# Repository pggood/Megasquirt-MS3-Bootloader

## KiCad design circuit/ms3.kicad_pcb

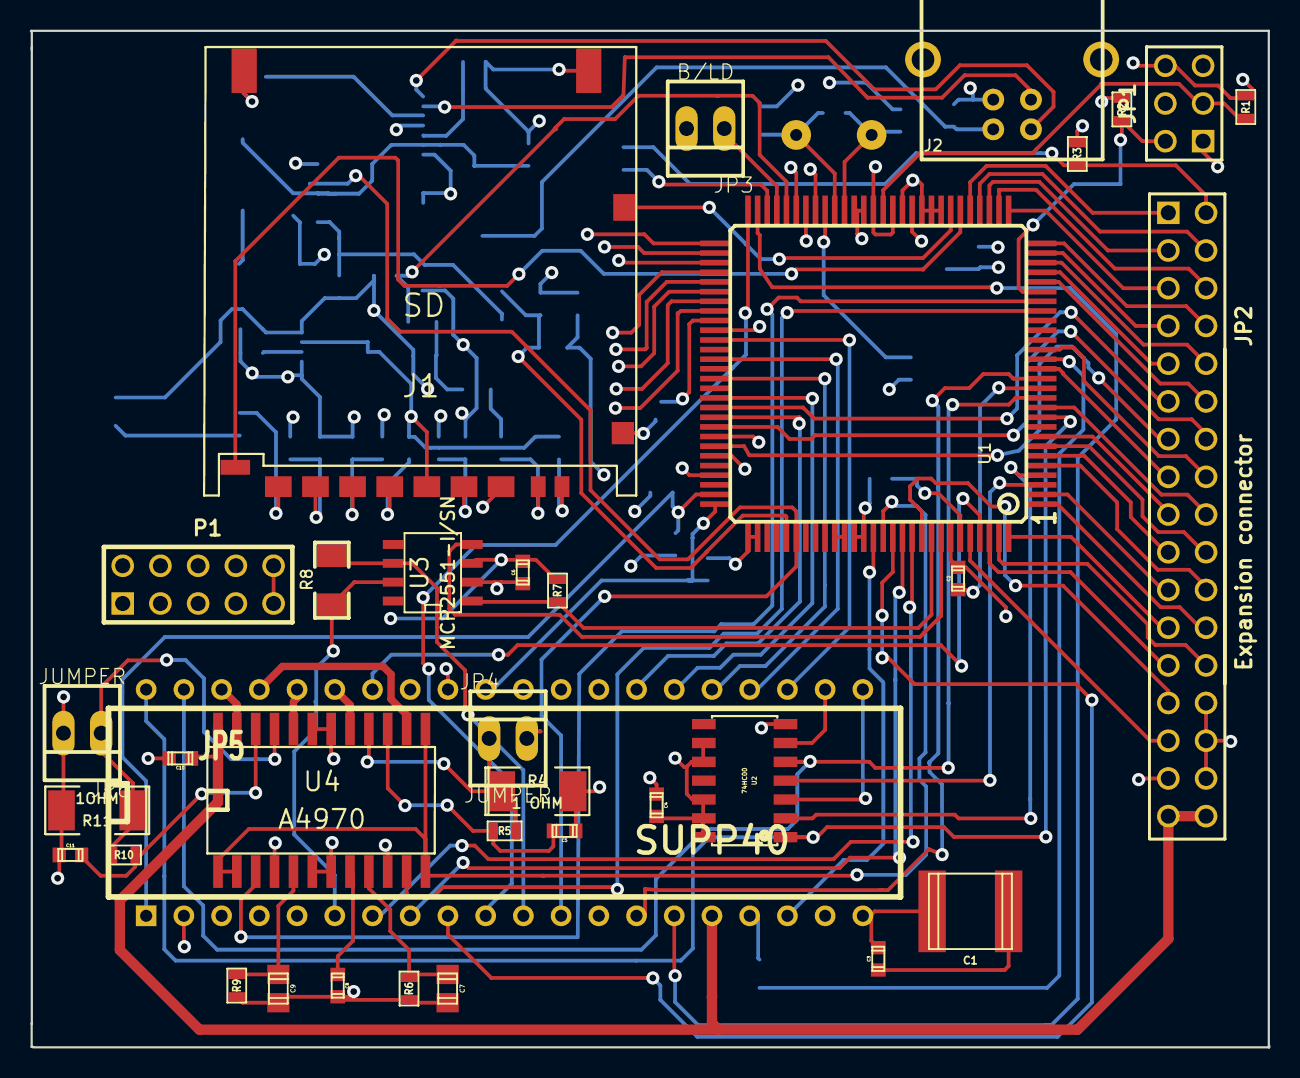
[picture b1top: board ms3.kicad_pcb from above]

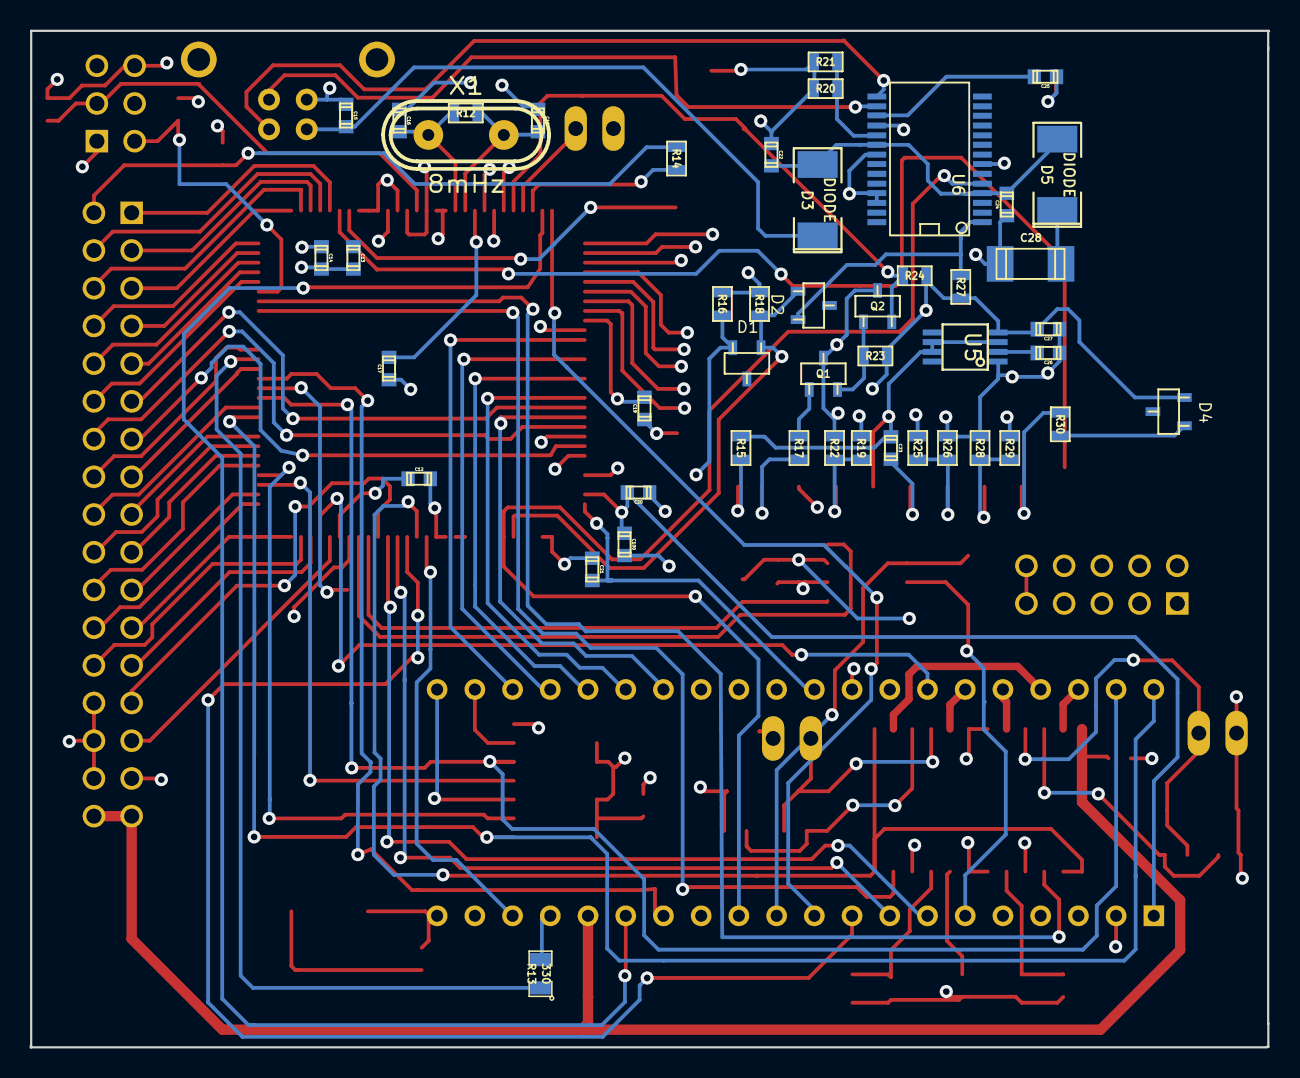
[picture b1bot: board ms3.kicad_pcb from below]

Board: 4 copper layers, 83.4 x 68.5 mm, 82 parts (47 on the bottom side), 123 nets.

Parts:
C1: 4.5uF; c_2220
C2, C21: 90nF; c_0603
C3, C4, C6, C20: .1; c_0603
C5, C11: 1nF; c_0603
C7, C9: 55nF; c_0805
C8, C10: 1.5uF; c_0603
C12, C13, C14, C100: .1uF; c_0603
C15: 10nF; c_0603
C16, C18: 50pF; c_0603
C17, C19: .2uF; c_0603
C22: 185nF; c_0603
C23, C26, C27: 1uF; c_0603
C24: 186nF; c_0603
C25: 100N; c_0603
C28: 4.7uF; c_1808
D1, D2, D4: DIODE; sot23
D3, D5: DIODE; SM2010
J1: SD; SDCARDmolex130203a
J2: USB_B
JP1: CONN_3X2; pin_array_3x2
JP2: Expansion connector; pin_array_17x2
JP3: B/LD; PINHEAD1-2
JP4, JP6: JUMPER; PINHEAD1-2
JP5: SUPP40; DIP-40__600
P1: CONN_5X2; PIN_ARRAY_5x2
Q1, Q2: 2N7002; sot23_v2
R1, R2, R21: 4K7; SM0603
R3, R14, R15, R16, R18, R20, R27: 10K; SM0603
R4: 1 OHM; SM2010
R5, R6, R7, R9, R10, R22, R23, R24, R26, R28: 1K; SM0603
R8: 120; SM1206
R11: 1OHM; SM2010
R12: 10M; SM0603
R13: 330; SM0805
R17, R19, R25, R29: 470; SM0603
R30: 10k; SM0603
U1: MC9S12XDP512; PQFP112
U2: 74HC00; SOP14
U3: MCP2551-I/SN; SO8E
U4: A4970; SOICW24
U5: LD1117LD33C; SSOP8
U6: FT232RL; SSOP28
X1: 8mHz; crystal_hc-49u

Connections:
+12V: C10.2, JP2.33, JP2.34, JP5.16, U4.24
/CPU/AD0-1: JP5.23, U1.67
/CPU/AD1-1: JP5.24, U1.69
/CPU/AD2-1: JP5.25, U1.71
/CPU/AD3-1: JP5.26, U1.73
/CPU/AD4-1: JP5.27, U1.75
/CPU/AD5-1: JP5.28, U1.77
/CPU/AD6-1: JP5.29, U1.79
/CPU/AD7-1: JP5.30, U1.81
/CPU/AN11: JP2.11, U1.74
/CPU/AN12: JP2.14, U1.76
/CPU/AN13: JP2.13, U1.78
/CPU/AccLed: JP5.8, U1.101
/CPU/CAM: JP2.18, U1.11
/CPU/CANrx: U1.105, U3.4
/CPU/CANtx: R7.2, U1.104, U3.1
/CPU/FLEX: R14.1, U1.54
/CPU/FP: JP5.33, U1.39
/CPU/IAC1: U1.21, U4.11
/CPU/IAC2: U1.22, U4.3
/CPU/IACEnble: U1.99, U4.1, U4.2, U4.12, U4.13
/CPU/IDLE: JP5.34, U1.109
/CPU/IGN: R13.1, U1.16
/CPU/IGN2: JP2.15, U1.15
/CPU/INJ1: JP5.40, U1.10, U2.1
/CPU/INJ2: JP5.39, U1.12, U2.5
/CPU/IRQ: JP5.15, U1.55
/CPU/InjLed: JP5.7, U1.102
/CPU/KnkEnbl: JP5.18, U1.98
/CPU/PA0: P1.1, U1.57
/CPU/PA1: P1.2, U1.58
/CPU/PA2: P1.3, U1.59
/CPU/PA3: P1.4, U1.60
/CPU/PA4: P1.5, U1.61
/CPU/PA5: P1.6, U1.62
/CPU/PA6: P1.7, U1.63
/CPU/PA7: P1.8, U1.64
/CPU/PB0: JP2.12, U1.24
/CPU/PB1: JP2.9, U1.25
/CPU/PB2: JP2.10, U1.26
/CPU/PB3: JP2.7, U1.27
/CPU/PB4: JP2.8, U1.28
/CPU/PB5: JP2.5, U1.29
/CPU/PB6: JP2.6, U1.30
/CPU/PB7: JP2.3, U1.31
/CPU/PH6: JP2.1, U1.33
/CPU/PH7: JP2.4, U1.32
/CPU/PK0: JP2.17, U1.8
/CPU/PK1: JP2.20, U1.7
/CPU/PK2: JP2.19, U1.6
/CPU/PK3: JP2.22, U1.5
/CPU/PK7: JP2.29, U1.108
/CPU/PM2: JP2.27, U1.103
/CPU/PP2: JP2.21, U1.2
/CPU/PP3: JP2.24, U1.1
/CPU/PP4: JP2.23, U1.112
/CPU/PP5: JP2.26, U1.111
/CPU/PP6: JP2.25, U1.110
/CPU/PT6: JP2.16, U1.17
/CPU/PWM1: U1.4, U2.2
/CPU/PWM2: U1.3, U2.4
/CPU/RESET: JP1.3, R1.1, U1.42
/CPU/RX: D1.1, D2.1, R18.1, U1.89
/CPU/SDCardCS: R29.2, U1.49
/CPU/SDCardInsert: J1.10, U1.34
/CPU/SDCardMISO: Q2.D, R24.2, U1.52
/CPU/SDCardMOSI: R25.2, U1.51
/CPU/SDCardSCLK: R19.2, U1.50
/CPU/TX: JP5.12, U1.90, U6.5
/CPU/VDDA: C20.1, C100.2, JP5.1, U1.83
/CPU/VREF: C21.1, JP5.31, U1.84
/CPU/VSS1: JP5.14, U1.14
/CPU/WarmLed: JP5.9, U1.100
/CPU/XIRQ: JP5.10, U1.56
/SDCARD/3.3V: C23.2, C26.1, J1.4, R15.2, U5.2, U5.3, U5.6, U5.7
/SDCARD/RXMS1: D1.2, JP5.13, R16.2
/SDCARD/SDCardLock: J1.12, U1.35
/ms1Interface/X2: JP5.38, U4.23
/ms1Interface/X3: JP5.37, U4.14
/ms1Interface/X4: JP5.36, U4.20
/ms1Interface/X5: JP5.35, U4.17
GND: C2.1, C4.2, C5.2, C6.2, C7.1, C8.1, C9.1, C10.1, C11.2, C12.1, C14.2, C15.2, C16.2, C17.2, C18.2, C19.2, C20.2, C21.2, C22.2, C23.1, C24.2, C25.2, C26.2, C27.2, C28.2, C100.1, J1.3, J1.6, J1.11, J1.13, J1.14, J2.4, J2.5, JP1.1, JP2.28, JP2.30, JP2.32, JP3.2, JP4.2, JP5.2, JP5.19, JP5.32, JP6.2, Q1.S, Q2.S, R4.2, R6.1, R9.1, R11.2, R20.1, R21.1, R22.2, R26.2, R28.2, U1.36, U1.37, U1.38, U1.40, U1.44, U1.45, U1.66, U1.85, U1.86, U1.94, U1.95, U1.96, U1.97, U1.106, U2.7, U3.2, U4.6, U4.7, U4.18, U4.19, U5.1, U6.7, U6.18, U6.21, U6.25, U6.26
unnamed: JP2.2, R3.1, R14.2
unnamed: P1.9, P1.10
unnamed: C11.1, R10.2, U4.22
unnamed: C5.1, R5.2, U4.15
unnamed: JP6.1, R10.1, R11.1, U4.21
unnamed: JP4.1, R4.1, R5.1, U4.16
unnamed: C1.1, C3.1, JP5.20
unnamed: C1.2, C3.2
unnamed: C7.2, R6.2, U4.9
unnamed: C9.2, R9.2, U4.5
unnamed: JP5.21, U2.3
unnamed: C8.2, U4.8
unnamed: JP5.17, R13.2
unnamed: JP5.6, R8.1, U3.7
unnamed: JP5.11, R8.2, U3.6
unnamed: JP5.22, U2.6
unnamed: C25.1, U6.17
unnamed: D2.2, R27.1, U6.1
unnamed: R20.2, R21.2, U6.19
unnamed: C28.1, D5.1
unnamed: D4.1, R30.1
unnamed: C15.1, D3.1, J2.1
unnamed: J1.2, R25.1, R26.1
unnamed: J1.1, R28.1, R29.1
unnamed: Q1.D, Q2.G, R23.2
unnamed: Q1.G, R17.2
unnamed: J1.5, R19.1, R22.1
unnamed: J1.9, R30.2
unnamed: J1.8, R15.1
unnamed: J1.7, R17.1
unnamed: J2.3, U6.16
unnamed: J2.2, U6.15
unnamed: C22.1, C24.1, D3.2, D5.2, U6.4, U6.20
unnamed: C19.1, U1.65
unnamed: JP3.1, U1.53
unnamed: C17.1, U1.48
unnamed: C16.1, R12.1, U1.46, X1.1
unnamed: C18.1, R12.2, U1.47, X1.2
unnamed: C2.2, U1.13
unnamed: JP1.2, R2.2, U1.23
VCC: C4.1, C6.1, C12.2, C13.1, C14.1, C27.1, D4.2, JP1.6, JP2.31, R1.2, R2.1, R3.2, R7.1, R16.1, R18.2, R23.1, R24.1, R27.2, U1.41, U1.43, U1.107, U2.9, U2.10, U2.12, U2.13, U2.14, U3.3, U4.4, U4.10, U5.4

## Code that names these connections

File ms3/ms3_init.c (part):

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                PWMPOL |= 0x08;
            }
        }
    } else if (pinsetting == 1) {  // Idle
        if (portusage->p[2]) {
            conf_err = feature_conferr;
                conf_err_feat = portusage->p[2];
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            *port = pPTT;
            *pin = 0x20;
        }
    } else if (pinsetting == 1) {     // on IAC1
        if (portusage->j[1]) {
            conf_err = feature_conferr;
                        conf_err_feat = portusage->j[1];
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            *port = pPTJ;
            *pin = 0x02;
        }
    } else if (pinsetting == 2) {      // on IAC2
        if (portusage->j[0]) {
            conf_err = feature_conferr;
                        conf_err_feat = portusage->j[0];
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            *port = pPTK;
            *pin = 0x01;
        }
    } else if (pinsetting == 8) {      // Idle on MS3X
        if (portusage->p[2]) {
            conf_err = feature_conferr;
                        conf_err_feat = portusage->p[2];
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    if (pin_match) {
        *pin_match = 0; // default is active low
    }
// "Off", "Tableswitch", "PE0/JS7", "PE1", "JS10", "JS11", "JS5 (ADC6)", "JS4 (ADC7)", "Nitrous In", "Launch in", "Datalog In", "PT4 Spare in", "PT2 Cam in", "PE2 Flex", "INVALID", "INVALID"
    if (pinsetting == 1) {  // TableSwitch
        if ((portusage->h[6]) && (feature_conferr)) {
            conf_err = feature_conferr;
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            *pin = 0x20;
        }
    } else if (pinsetting == 5) { // JS11
        //JS11 was PA0 on MS2/Extra. Now connected to PJ7
        if ((portusage->j[7]) && (feature_conferr)) {
            conf_err = feature_conferr;
            conf_err_feat = portusage->j[7];
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                *pin_match = *pin; // nitrous is active high
            }
        }
    } else if (pinsetting == 9) {      //  PK2 Launch in
        if ((portusage->k[2]) && (feature_conferr)) {
            conf_err = feature_conferr;
            conf_err_feat = portusage->k[2];
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            TFLG1 = 0x10;
            TIE |= 0x10;
        }
    } else if (pinsetting == 1) {  // MS3X PT2 cam input
        if (portusage->t[2]) {
            conf_err = feature_conferr;
            conf_err_feat = portusage->t[2];
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            TFLG1 = 0x04;
            TIE |= 0x04;
        }
    } else if (pinsetting == 2) {  // JS10 PT5 cam input
        if (portusage->t[5]) {
            conf_err = feature_conferr;
            conf_err_feat = portusage->t[5];
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            TFLG1 = 0x20;
            TIE |= 0x20;
        }
    } else if (pinsetting == 3) {  // Datalog PT6 cam input
        if (portusage->t[6]) {
            conf_err = feature_conferr;
            conf_err_feat = portusage->t[6];
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    DDRC = 0;                   // non bonded input
    DDRD = 0;                   // non bonded input
    RDRIV = 0;                  // full strength
//    DDRH = 0x08;                // SD card. inputs PH0-5, except PH3/SS as output.  Spares PH6,7 set as input
    PERH = 0x30;                // pulls on PH4,5
    PPSH = 0x00;                // pullUP devices
//    DDRJ = 0x43;                // bits 0,1,6 are outputs
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    flash_Miss_ang = ram4.Miss_ang;

    if (((ram4.EngStroke & 0x03) == 0x03) && (cycle_deg == 7200)) {
        conf_err = 44;      // rotary doesn't need 720deg i.e. cam speed reset
    }

    if (((ram4.EngStroke & 0x03) == 0x03) && (num_cyl > 2) &&
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    if (ram4.hardware & HARDWARE_MS3XSPK) {
        // using MS3X for spark
        if (num_spk) {
        portusage.b[0] = 10; //PB0
        port_inits_PORTB |= (uc1 ^ 0x01) & 0x01;
        DDRB |= 0x01;
        }
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            || ((spkmode == 2) && ((ram4.spk_conf2 & 0x07) == 0x01)) // basic trigger + bypass
            || ((spkmode == 4) && ((ram4.spk_conf2 & 0x07) == 0x02))) { // toothed wheel + C3I
            // >=2 coils or HEI bypass
            portusage.b[1] = 10;     //PB1
            port_inits_PORTB |= (uc1 ^ 0x02) & 0x02;
            DDRB |= 0x02;
        }
        if (num_spk >= 3) {
            portusage.b[2] = 10;     //PB2
            port_inits_PORTB |= (uc1 ^ 0x04) & 0x04;
            DDRB |= 0x04;
        }
        if (num_spk >= 4) {
            portusage.b[3] = 10;     //PB3
            port_inits_PORTB |= (uc1 ^ 0x08) & 0x08;
            DDRB |= 0x08;
        }
        if (num_spk >= 5) {
            portusage.b[4] = 10;     //PB4
            port_inits_PORTB |= (uc1 ^ 0x10) & 0x10;
            DDRB |= 0x10;
        }
        if (num_spk >= 6) {
            portusage.b[5] = 10;     //PB5
            port_inits_PORTB |= (uc1 ^ 0x20) & 0x20;
            DDRB |= 0x20;
        }
        if (num_spk >= 7) {
            portusage.b[6] = 10;     //PB6
            port_inits_PORTB |= (uc1 ^ 0x40) & 0x40;
            DDRB |= 0x40;
        }
        if (num_spk >= 8) {
            portusage.b[7] = 10;     //PB7
            port_inits_PORTB |= (uc1 ^ 0x80) & 0x80;
            DDRB |= 0x80;
        }
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                OCPD |= 0x20;
                port_spki = &PTT;
                pin_spki = 0x20;
            } else { // PK0 Tacho (for MSD white wire)
                portusage.k[0] = 10;    //PK0
                port_inits_PORTK |= (uc1 ^ 0x01) & 0x01;
                port_inits_DDRK |= 0x01;
                DDRK |= 0x01; // ensure port set as output
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    /* default ports */
    port_iacen = &PTJ;

    // Allocate IAC or PWM idle pins
    /* first convert from broken-out idle settings to old number */
    IdleCtl = ram4.IdleCtl & 0x3;
    if (IdleCtl == 2) {
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    
    // Flex fuel input
    flexblend = 0;
    pin_flex = 0;
    if (ram4.FlexFuel & 0x1) {
        /* 0=PE0, 2 = PE1, 4 = PE2, 5 = n/a */
        if ((ram4.FlexFuel & 0x6) == 0) {
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                conf_err = 5;
            } else {
                portusage.e[0] = 58;
                pin_flex = 1;
            }
        } else if ((ram4.FlexFuel & 0x6) == 2) {
            if (portusage.e[1]) {
                conf_err = 5;
            } else {
                portusage.e[1] = 58;
                pin_flex = 2;
            }
        } else {                // use MS3X input
            if (portusage.e[2]) {
                conf_err = 5;
            } else {
                portusage.e[2] = 58;
                pin_flex = 4;
            }
        }
    }
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        }
        als_duty_pwm = 0;

        if ((ram_window.pg24.als_opt & 0x21) &&  // fuel cut or roving-idle
            (! ((ram4.hardware & HARDWARE_MS3XFUEL) && (glob_sequential & (SEQ_SEMI | SEQ_FULL))) )) {
            /* Cannot use fuel cut if not in MS3X sequential */
            conf_err = 142;
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                }

                /* set to 'rest' positions */
                if ((ram_window.pg24.vvt_opt5 & twopow[i + 4]) // this cam is exhaust
                    && (ram_window.pg24.vvt_opt1 & 0x80)) { // exhaust table is a retard table
                    ang = ram_window.pg24.vvt_max_ang[i];
                } else {
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            conf_err = 124;
            conf_err_feat = portusage.k[3];
        } else {
            DDRK &= ~2; // PK1 input  SDA. Pullup already enabled earlier
            DDRK |= 8; // PK3 output SCL
            PORTK |= 8; //SCL high
            portusage.k[1] = 106;
            portusage.k[3] = 106;
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            if ((MONVER >= 0x390) && (MONVER <= 0x39f)) {
                DDRK |= 0x80;
                pin_knock_out = 0x80;
                port_knock_out = &PORTK; // hardcoded to PK7 for deriv#3
            } else {
                generic_digout_setup(&port_knock_out, &pin_knock_out, 4, tmp_opt, 12);
            }
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                    pin_knk = 0x20;
                }
            } else if (tmp_opt == 5) { // JS11
                //JS11 was PA0 on MS2/Extra. Now connected to PJ7
                if (portusage.j[7]) {
                    conf_err = 4;
                } else {
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                    port_knk = pPTH;
                    pin_knk = 0x80;
                }
            } else if (tmp_opt == 9) {      //  PK2 Launch in
                if (portusage.k[2]) {
                    conf_err = 4;
                } else {
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
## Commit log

2016-01-24 Initial files as downloaded from Megasquirt.
2016-01-24 Couple of Slickedit workspace/project files. About to be ignored.
2016-01-24 Made the fan control code more readable.
2016-01-24 Ignore some Slickedit files.
2016-01-24 Remove some Slickedit files from the repo.
2016-01-24 Added sliding average module to simplying ADC averaging code. Wouldn't be surprised to find it smaller and faster than the original code.
2016-01-25 Changed the sliding window average module a little. Should remove an unneeded division.
2016-01-25 Fixed a type. Moved a macro.
2016-01-25 Removed some redundant code.
2016-01-26 Got the firmware building.
2016-01-26 Remove some files relating to slickedit.
2016-01-26 Ignore some build artifacts.
2016-01-26 More Makefile changes to remove some make warnings.
2016-01-26 Added some macros in ms3_idle.c to abstract some things out a little.
2016-01-28 Abstracted out the overrun states.
2016-01-29 Replaced references to redundant (well, I think it is) FLAGBYTE17_OVERRUNFC by checking the overrun state directly.
2016-01-30 Removed redundant setting of boostduty within open loop and closed loop calculations as it's done anyway after those functions return.
2016-01-30 Abstracted out some more things relating to overrun fuel cut.
2016-01-30 Abstracted out some of the system tick values representing 1 seccond or some fraction of it.
2016-01-30 Made global function static, which reduced teh size of the .o file a wee bit.
2016-01-30 Simplified the code a little in ms3_ign.c to remove unnecessary duplicate tests.
2016-01-30 Made global function static, which reduced teh size of the .o file a wee bit. (reverted from commit f9512e0994b514c43162fd157a216abb3ece7a34)
2016-01-30 Ignore a couple of build artifacts.
2016-01-30 Sliding window average code seems a little more simple when uint8_t integer types are used instead of size_t (16 bit).
2016-01-31 Made [id helper function static to reduce its scope.
2016-01-31 Generic PID variabls are now grouped into their own structure, rather than have a pair of variables for each field.
2016-01-31 Variables previously prefixed with fc are now prefixed with fuel_cut to make it clearer what they refer to.
2016-01-31 Ignore some slickedit files
2016-01-31 Split overrun calculations function into two to make it easier to follow.
2016-02-01 Abstracted out required battery voltage required for fan.
2016-02-01 Abstracted out GPIO pin testing. Now makes use of a GPIO_ACTIVE() macro to test if a pin is active.
2016-02-01 Removed a few shift operations and replaced with multiply/divide so as to leave it up to the compiler to optimise these into shifts.
2016-02-02 shift_cut_in input now uses GPIO_ACTIVE macro.
2016-02-02 Using macro to convert percentage values to some other scale in a few places.
2016-02-02 Reverted some of the previous commit's changes because I was unsure if there would be any overflow/sign issues with them. Also removed a few warnings that occur with different optimisation levels.
2016-02-02 Altered the GPIO ON/OFF macros. Altered the fan control macros so that status updates are always done separately.
2016-02-02 Using GPIO ON/OFF macros to control all gpio outputs.
2016-02-02 Refactored a bit of logic in ms3_can.c. This makes the code a bit easier to read, and also makes the code smaller.
2019-07-23 this is the first 64k of a MS3
    Needs to be loaded into the base of ms3 hc11 inorder to boot the MS3
2019-07-25 Removed as requested by JM Cortina
2022-02-15 Add files via upload
    MON for ms2

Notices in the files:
ms3/ms3_init.c:
Copyright 2007, 2008, 2009, 2010, 2011, 2012 James Murray and Kenneth Culver
